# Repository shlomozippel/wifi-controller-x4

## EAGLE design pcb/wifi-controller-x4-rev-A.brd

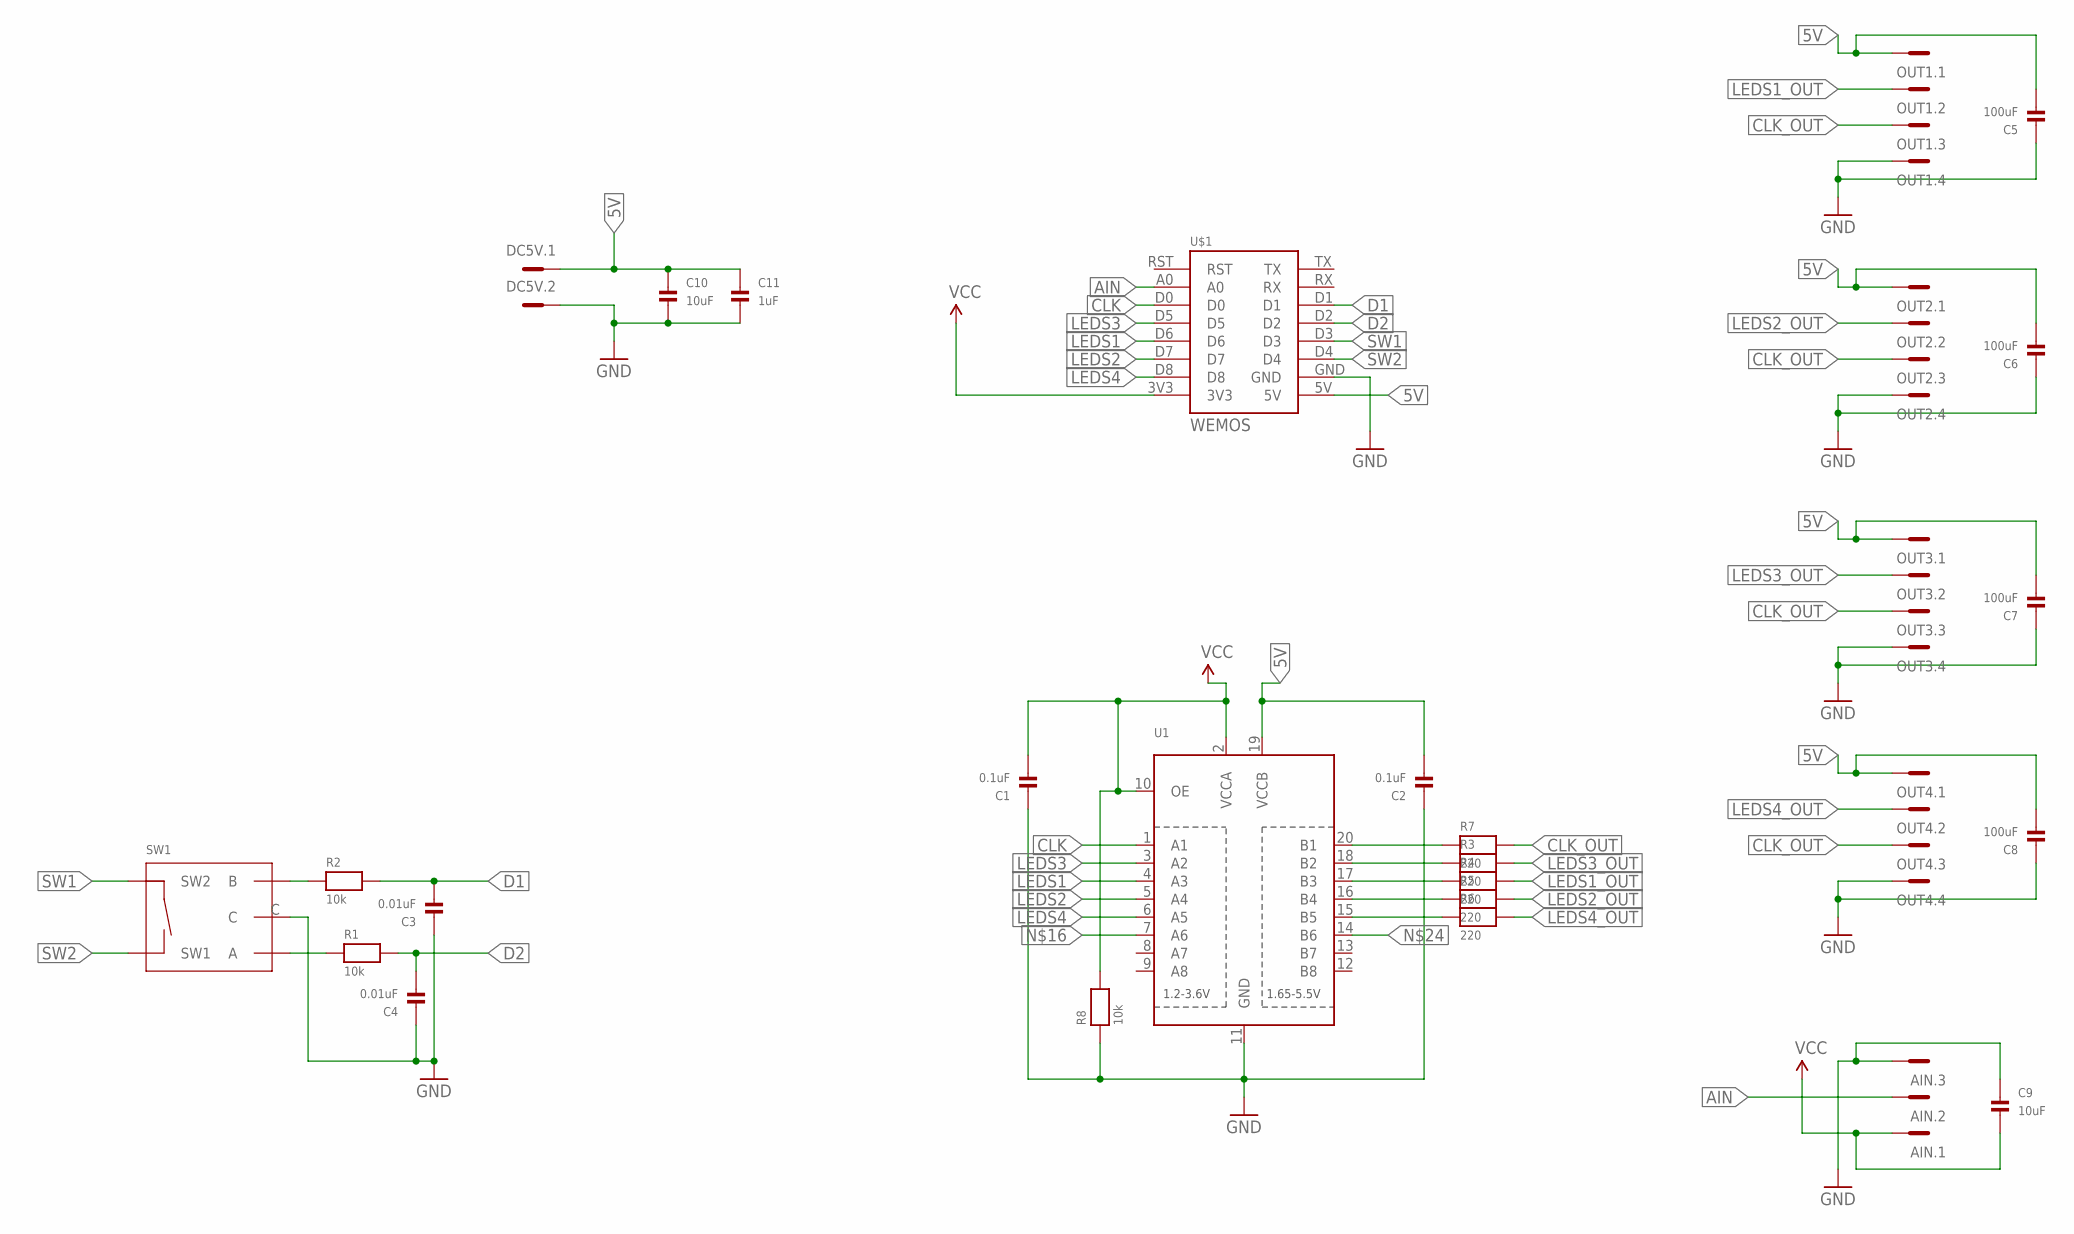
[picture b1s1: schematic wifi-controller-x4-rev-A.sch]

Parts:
AIN: MC3
C1, C2: 0.1uF; 0603
C3, C4: 0.01uF; 0603
C5, C6, C7, C8: 100uF; 1206
C9, C10: 10uF; 0603
C11: 1uF; 0603
DC5V: MC2
OUT1, OUT2, OUT3, OUT4: MC4
R1, R2, R8: 10k; 0603
R3, R4, R5, R6, R7: 220; 0603
SW1: ROTARY-ENCODER-BOURNS-PEC11S; PEC11S
U1: TXB0108PWR; TSSOP20
U$1: WEMOS

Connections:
5V: C2.2, C5.2, C6.2, C7.2, C8.2, C10.1, C11.1, DC5V.1, OUT1.1, OUT2.1, OUT3.1, OUT4.1, U1.19 (VCCB), U$1.5V
AIN: AIN.2, U$1.A0
CLK: U1.1 (A1), U$1.D0
CLK_OUT: OUT1.3, OUT2.3, OUT3.3, OUT4.3, R7.2
D1: C3.2, R2.2, U$1.D1
D2: C4.2, R1.2, U$1.D2
GND: AIN.3, C1.1, C2.1, C3.1, C4.1, C5.1, C6.1, C7.1, C8.1, C9.1, C10.2, C11.2, DC5V.2, OUT1.4, OUT2.4, OUT3.4, OUT4.4, R8.1, SW1.C, U1.11 (GND), U$1.GND
LEDS1: U1.4 (A3), U$1.D6
LEDS1_OUT: OUT1.2, R4.2
LEDS2: U1.5 (A4), U$1.D7
LEDS2_OUT: OUT2.2, R5.2
LEDS3: U1.3 (A2), U$1.D5
LEDS3_OUT: OUT3.2, R3.2
LEDS4: U1.6 (A5), U$1.D8
LEDS4_OUT: OUT4.2, R6.2
unnamed: R7.1, U1.20 (B1)
unnamed: R3.1, U1.18 (B2)
unnamed: R2.1, SW1.B
unnamed: R4.1, U1.17 (B3)
unnamed: R5.1, U1.16 (B4)
unnamed: R1.1, SW1.A
unnamed: R6.1, U1.15 (B5)
SW1: SW1.E (SW2), U$1.D3
SW2: SW1.D (SW1), U$1.D4
VCC: AIN.1, C1.2, C9.2, R8.2, U1.2 (VCCA), U1.10 (OE), U$1.3V3

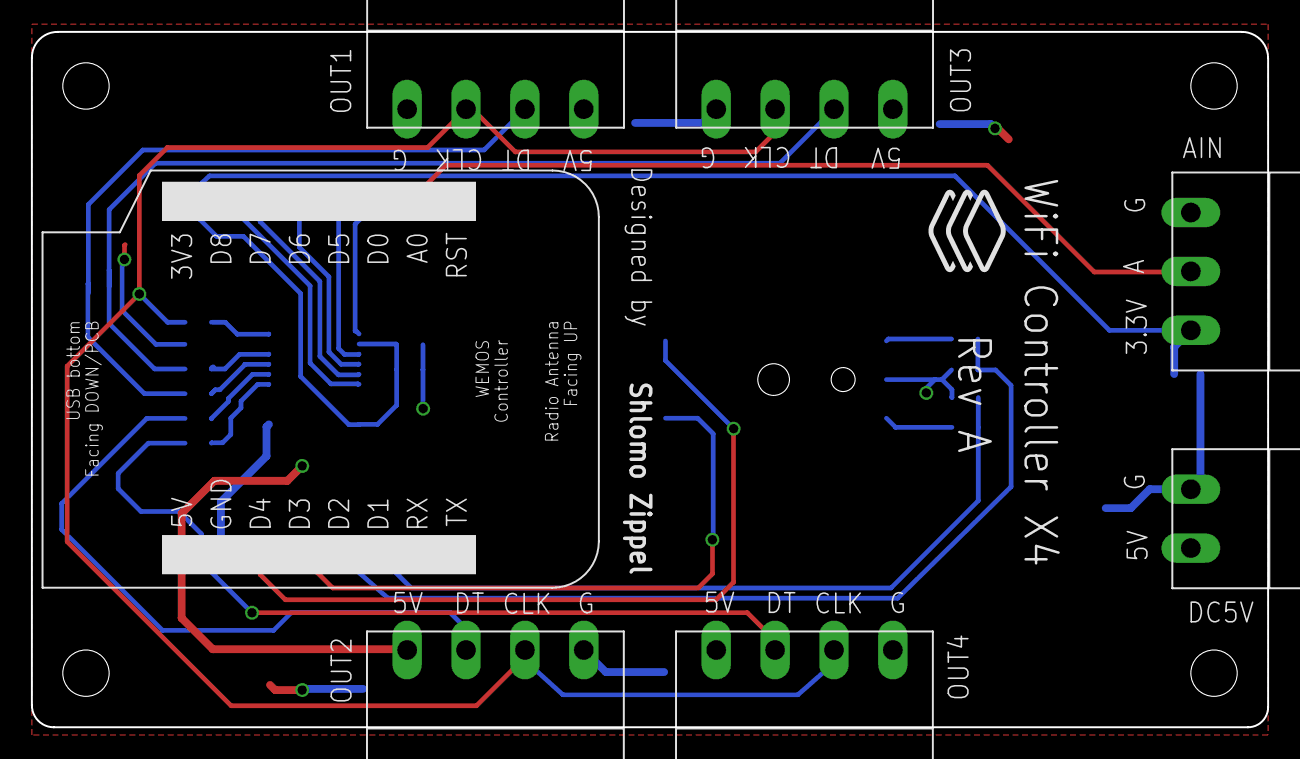
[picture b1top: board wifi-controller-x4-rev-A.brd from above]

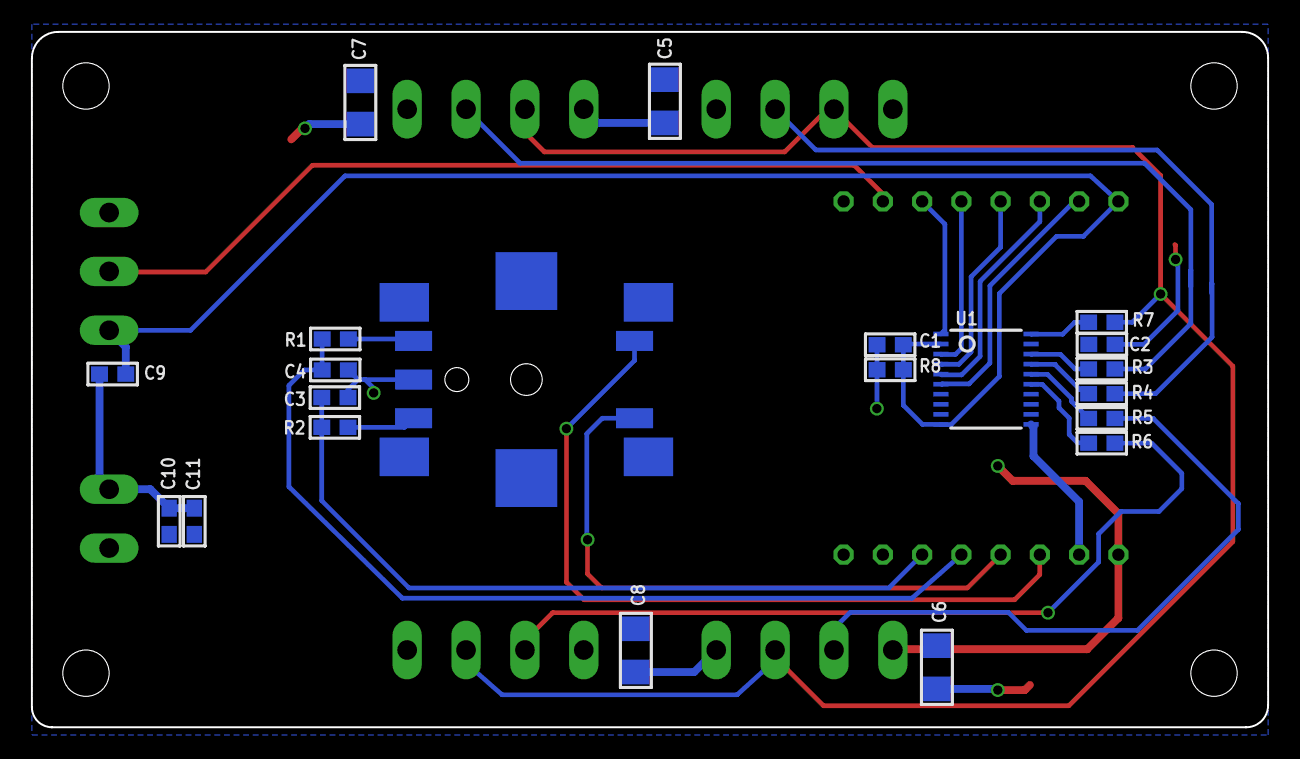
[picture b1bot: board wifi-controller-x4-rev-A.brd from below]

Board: 2 copper layers, 80.0 x 45.0 mm, 29 parts (21 on the bottom side), 25 nets.

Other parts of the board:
U$8: 86*51

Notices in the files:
parts and their libraries:
microbuilder: This work is placed in the public domain, and may be freely used for commercial and non-commercial work with the following conditions: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
SparkFun-Aesthetics: Licensing: Creative Commons ShareAlike 4.0 International - https://creativecommons.org/licenses/by-sa/4.0
